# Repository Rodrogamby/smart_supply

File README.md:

# Dashboard

Dashboard for the project, built with HTML, CSS, JavaScript, Vite, and MQTT.js

The current prototype displays real sensor readings from an ESP32-S3 in the Channel 1 area

## Requirements

- Install [Node.js](https://nodejs.org/) with npm 
- An internet connection to reach the MQTT broker already running on Azure
- An ESP32 publishing measurements to see live readings

## Install and run

Open a terminal in the GUI folder containing `package.json`.

```sh
npm install
npm run dev
```

`npm install` installs the project's dependencies, including Vite and MQTT.js, and creates `node_modules`. 

Open the local URL printed by Vite. Keep the terminal running while using the dashboard. Press **Ctrl+C** to stop it; use `npm run dev` to start it again.

## Connect to MQTT

Enter these values in the dashboard and click **Connect**:

| Setting | Value |
| --- | --- |
| WebSocket URL | `wss://retotest.mexicocentral.cloudapp.azure.com:8084/mqtt` |
| Current test username | `reto` |
| Current test password | `reto` |
| Topic used by the JavaScript | `test2` |

These are temporary lol

The ESP32 sends MQTT over TLS on port **8883**. The browser uses MQTT over secure WebSockets on port **8084** to connect to the same broker.

## Measurement format

The ESP32 publishes JSON messages like this on `test2`:

```json
{
  "device": "device",
  "sensor": "sensor",
  "sample": 1,
  "adc_raw": 25798
}
```

## Project files

| File | Purpose |
| --- | --- |
| `index.html` | Dashboard structure |
| `src/style.css` | Styling and responsive layout |
| `src/main.js` | MQTT connection, message validation, and display updates |
| `package.json` | Dependencies and npm commands |
| `package-lock.json` | Locked dependency versions |

# Access the Virtual Machine

Use Tec Visitantes Network

```cmd
ssh -i "path of the  smart_supply\VM\vm1_key.pem file" azureuser@158.23.60.51
```

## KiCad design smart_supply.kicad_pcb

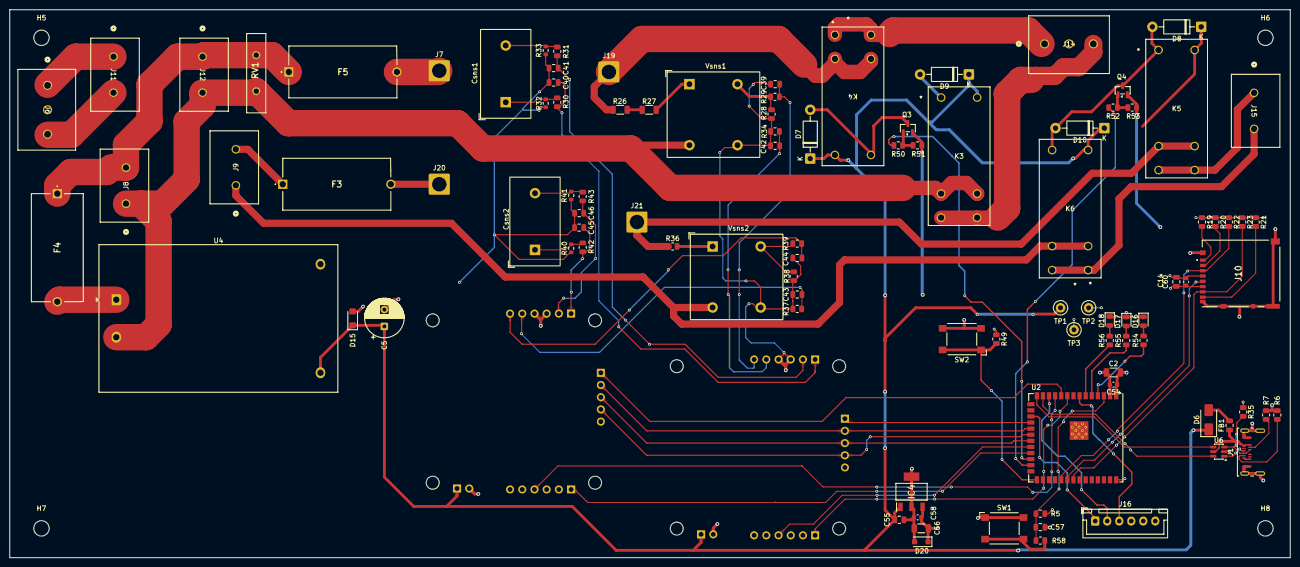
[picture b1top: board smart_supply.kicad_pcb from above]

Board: 4 copper layers, 266.5 x 114.0 mm, 106 parts (0 on the bottom side), 76 nets.

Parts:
C2: 22u; C_1206_3216Metric
C5: 220u; CP_Radial_D8.0mm_P3.50mm
C14: 10u; C_0805_2012Metric
C39, C40, C41, C42, C43, C44, C45, C46: 33n; C_0805_2012Metric
C54, C58, C60: 100n; C_0603_1608Metric
C55: 4.7u; C_0805_2012Metric
C56: 10u; C_1206_3216Metric
C57: 1uF; C_0805_2012Metric
Csns1, Csns2: ZMCT103C; Transformer_Zeming_ZMCT103C
D6: SS34; D_SMA
D7, D8, D9, D10: 1N4007; D_DO-41_SOD81_P10.16mm_Horizontal
D15: SMF5V0A; D_SMF
D16, D17, D18: LED; LED_0805_2012Metric
D20: SMF3.3; D_SOD-123F
F3, F4, F5: Fuse; fuse holder
FB1: FerriteBead; C_0805_2012Metric
H5, H6, H7, H8: MountingHole; MountingHole_3.2mm_M3
IC4: MIC39100-3.3WS; SOT230P700X180-4N
J1: USB_C_Receptacle_USB2.0_16P; USB_C_Receptacle_Amphenol_124019772112A
J6, J14: 1730405; CONN_1730405_PXC
J7, J19, J20, J21: Conn_01x01; SolderWire-2.5sqmm_1x01_D2.4mm_OD4.4mm
J8, J9, J11, J12, J15: 1717020; CONN_1717020_PXC
J10: DM3AT-SF-PEJM5; DM3ATSFPEJM5
J16: Conn_01x06_Pin; JST_XH_B6B-XH-A_1x06_P2.50mm_Vertical
J17, J18: Conn_01x19_Pin; breakoutHOLES
K3, K4, K5, K6: G2R-1A-E DC5; RELAY_G2R-1A-E AC12_OMR
Q3, Q4: AO3400A; SOT-23
R5, R19, R20, R21, R22, R23, R49: 10k; R_0805_2012Metric
R6, R7: 5.1k; R_0805_2012Metric
R26, R27: 47k; R_1206_3216Metric
R28, R38, R50, R52: 100; R_0805_2012Metric
R29, R30, R31, R34, R37, R39, R42, R43: 1k; R_0805_2012Metric
R32, R33: 10; R_0603_1608Metric
R35: 1.5k; R_0805_2012Metric
R36: 20k; R_0805_2012Metric
R40, R41: 33; R_0603_1608Metric
R51, R53: 100k; R_0805_2012Metric
R54, R55, R56, R58: 470; R_0805_2012Metric
RV1: MOV-14D241K; MOV14D241K
SW1, SW2: SW_Push; SW_SPST_Omron_B3FS-100xP
TP1, TP2, TP3: TestPoint; TestPoint_Loop_D2.50mm_Drill1.0mm
U2: ESP32-S3-WROOM-1U
U4: HLK-10M05; Converter_ACDC_Hi-Link_HLK-10Mxx
U6: USBLC6-2SC6; SOT-23-6
Vsns1, Vsns2: ZMPT101K; Transformer_Zeming_ZMPT101K

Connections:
+3.3V: C2.1, C14.1, C54.1, C56.1, C58.2, C60.2, D20.1 (A1), IC4.3 (OUT), J10.4 (VDD), R5.2, R19.1, R20.1, R21.1, R22.1, R23.1, R35.1, R49.1, TP2.1 (1_1), U2.2 (3V3)
+5V: C5.1, C55.1, D6.1 (K), D7.1 (K), D8.1 (K), D9.1 (K), D10.1 (K), D15.1 (A1), IC4.1 (IN), J17.19, J18.19, K3.8, K4.8, K5.8, K6.8, TP1.1 (1_1), U4.4 (+Vout)
/MCU/BOOT: R49.2, SW2.1, U2.27 (IO0)
/MCU/CLK_SD: J10.5 (CLK), U2.32 (IO39)
/MCU/CMD: J10.3 (CMD), R22.2, U2.31 (IO38)
/MCU/D0_SD: J10.7 (DAT0), R23.2, U2.33 (IO40)
/MCU/DAT1: J10.8 (DAT1), R21.2
/MCU/DAT2: J10.1 (DAT2), R19.2
/MCU/DAT3: J10.2 (CD/DAT3), R20.2
/MCU/EN: C57.2, R5.1, R58.2, U2.3 (EN)
/MCU/FUSEL: F4.2, U4.1 (AC/L)
/MCU/LEDF: R55.1, U2.5 (IO5)
/MCU/LEDSD: R56.1, U2.6 (IO6)
/MCU/LEDW: R54.1, U2.4 (IO4)
/MCU/USB_D+: U2.14 (USB_D+), U6.4 (I/O2)
/MCU/USB_D-: U2.13 (USB_D-), U6.6 (I/O1)
/MCU/VBUS: FB1.1, J1.A4 (VBUS), J1.A9 (VBUS), J1.B4 (VBUS), J1.B9 (VBUS), U6.5 (VBUS)
/POWER LINES/CH1_L_OUT: J14.1, K4.4, K4.5
/POWER LINES/CH1_N_OUT: J14.3, K3.4, K3.5
/POWER LINES/CH2_L: J21.1 (Pin_1_1), K5.3, K5.6, R36.1
/POWER LINES/CH2_L_OUT: J15.1, K5.4, K5.5
/POWER LINES/CH2_N: J9.1, K6.3, K6.6, Vsns2.2
/POWER LINES/CH2_N_OUT: J15.2, K6.4, K6.5
/POWER LINES/CT1_1: F5.2, J7.1 (Pin_1_1)
/POWER LINES/CT1_2: F3.2, J20.1 (Pin_1_1)
/POWER LINES/L: J6.1, J11.1
/POWER LINES/N: J6.3, J11.2
/POWER LINES/csns1P1: Csns1.1, R30.2, R32.1
/POWER LINES/csns1P2: Csns1.2, R31.2, R33.2
/POWER LINES/csns2P1: Csns2.1, R40.1, R42.2
/POWER LINES/csns2P2: Csns2.2, R41.2, R43.2
ACDCsupply: F4.1, F5.1, J8.2, J12.1, RV1.2
CH1_L: J19.1 (Pin_1_1), K4.3, K4.6, R26.1
CH1_N: J8.1, J12.2, K3.3, K3.6, RV1.1, U4.2 (AC/N), Vsns1.2
CS1: J17.7, U2.18 (IO10)
CS2: J18.7, U2.10 (IO17)
GND: C2.2, C5.2, C14.2, C39.2, C40.2, C41.2, C42.2, C43.2, C44.2, C45.2, C46.2, C54.2, C55.2, C56.2, C57.1, C58.1, C60.1, D15.2 (A2), D16.1 (K), D17.1 (K), D18.1 (K), D20.2 (A2), IC4.2 (GND_1), IC4.4 (GND_2), J1.A1 (GND), J1.A12 (GND), J1.B1 (GND), J1.B12 (GND), J1.SH (SHIELD), J10.6 (VSS), J10.MP1, J10.MP2, J10.MP3, J10.MP4, J10.MP5, J10.MP6, J16.6, J17.3, J17.4, J17.18, J18.3, J18.4, J18.18, Q3.2 (S), Q4.2 (S), R6.2, R7.2, R28.1, R32.2, R33.1, R34.2, R37.2, R38.2, R40.2, R41.1, R51.2, R53.2, SW1.1, SW2.2, TP3.1 (1_1), U2.1 (GND), U2.40 (GND), U2.41 (GND), U4.3 (-Vout), U6.2 (GND), Vsns1.3, Vsns2.3
IAN1: C41.1, J17.2, R31.1
IAN2: C46.1, J18.2, R43.1
IAP1: C40.1, J17.1, R30.1
IAP2: C45.1, J18.1, R42.1
IRQ1: J17.15, U2.22 (IO14)
IRQ2: J18.15, U2.11 (IO18)
LED1: J16.3, U2.7 (IO7)
LED2: J16.2, U2.12 (IO8)
LED3: J16.1, U2.17 (IO9)
MISO: J17.9, J18.9, U2.21 (IO13)
MOSI: J17.8, J18.8, U2.19 (IO11)
unnamed: D6.2 (A), FB1.2
unnamed: D7.2 (A), D9.2 (A), K3.1, K4.1, Q3.3 (D)
unnamed: D8.2 (A), D10.2 (A), K5.1, K6.1, Q4.3 (D)
unnamed: D16.2 (A), R54.2
unnamed: D17.2 (A), R55.2
unnamed: D18.2 (A), R56.2
unnamed: F3.1, J9.2
unnamed: J1.A5 (CC1), R6.1
unnamed: J1.B5 (CC2), R7.1
unnamed: J1.A6 (D+), J1.B6 (D+), R35.2, U6.3 (I/O2)
unnamed: J1.A7 (D-), J1.B7 (D-), U6.1 (I/O1)
unnamed: Q3.1 (G), R50.1, R51.1
unnamed: Q4.1 (G), R52.1, R53.1
unnamed: R26.2, R27.1
unnamed: R27.2, Vsns1.1
unnamed: R28.2, R29.2, Vsns1.4
unnamed: R36.2, Vsns2.1
unnamed: R38.1, R39.1, Vsns2.4
unnamed: R58.1, SW1.2
RLY_CH1: R50.2, U2.24 (IO47)
RLY_CH2: R52.2, U2.25 (IO48)
SCLK: J17.10, J18.10, U2.20 (IO12)
VN1: C42.1, J17.5, R34.1
VN2: C43.1, J18.5, R37.1
VP1: C39.1, J17.6, R29.1
VP2: C44.1, J18.6, R39.2
ZX1: J17.12, U2.9 (IO16)
ZX2: J18.12, U2.23 (IO21)

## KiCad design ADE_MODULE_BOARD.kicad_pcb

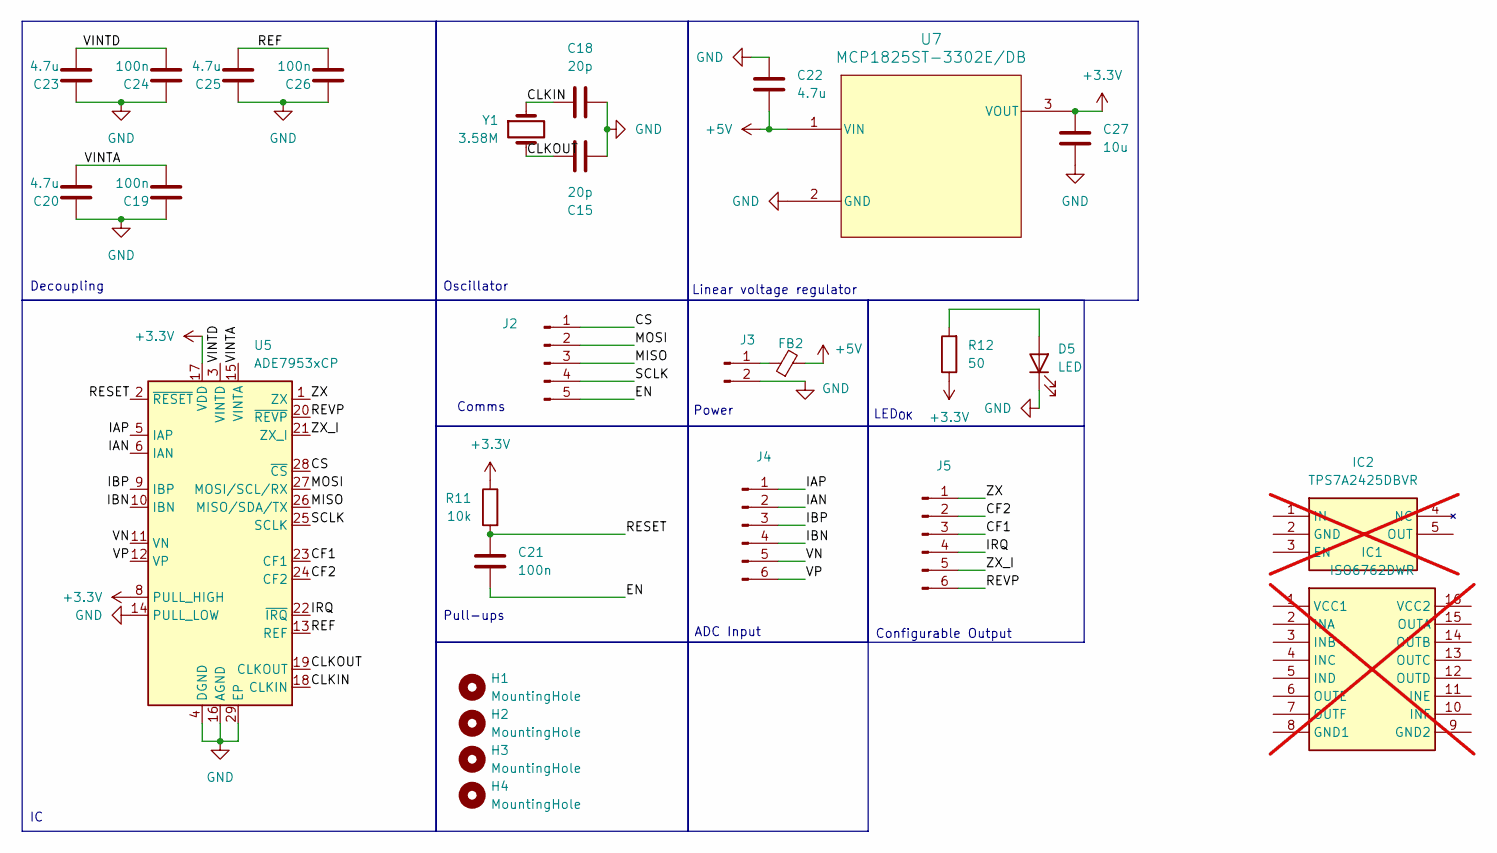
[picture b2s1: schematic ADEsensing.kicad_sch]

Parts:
C15, C18: 20p; C_0603_1608Metric; MPN C165732
C19, C21, C24, C26: 100n; C_0603_1608Metric; MPN C1590
C20, C22, C23, C25: 4.7u; C_0805_2012Metric; MPN C1779
C27: 10u; C_0805_2012Metric; MPN C15850
D5: LED; LED_0805_2012Metric; MPN C2986046
FB2: FerriteBead_Small; L_0805_2012Metric; MPN C1015
H1, H2, H3, H4: MountingHole; MountingHole_2.7mm_M2.5
IC1: ISO6762DWR; SOIC127P1030X265-16N; Mouser Part Number 595-ISO6762DWR; not fitted
IC2: TPS7A2425DBVR; SOT95P280X145-5N; Mouser Part Number 595-TPS7A2425DBVR; not fitted
J2: Conn_01x05_Pin; PinHeader_1x05_P2.54mm_Vertical
J3: Conn_01x02_Pin; PinHeader_1x02_P2.54mm_Vertical
J4, J5: Conn_01x06_Pin; PinHeader_1x06_P2.54mm_Vertical
R11: 10k; R_0805_2012Metric; MPN C17414
R12: 50; R_0805_2012Metric; MPN C55205334
U5: ADE7953xCP; LFCSP-28-1EP_5x5mm_P0.5mm_EP3.14x3.14mm_ThermalVias; MPN C515890
U7: MCP1825ST-3302E/DB; SOT-223-3_TabPin2; MPN C145411
Y1: 3.58M; Crystal_SMD_HC49-SD; MPN C22464956

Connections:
+3.3V: C27.1, R11.1, R12.1, U5.7 (PULL_HIGH), U5.8 (PULL_HIGH), U5.17 (VDD), U7.3 (VOUT)
+5V: C22.2, FB2.2, U7.1 (VIN)
/ADE Module/CF1: J5.3, U5.23 (CF1)
/ADE Module/CF2: J5.2, U5.24 (CF2)
/ADE Module/CLKIN: C18.1, U5.18 (CLKIN), Y1.1
/ADE Module/CLKOUT: C15.2, U5.19 (CLKOUT), Y1.2
/ADE Module/CS: J2.1, U5.28 (~CS)
/ADE Module/EN: C21.2, J2.5
/ADE Module/IAN: J4.2, U5.6 (IAN)
/ADE Module/IAP: J4.1, U5.5 (IAP)
/ADE Module/IBN: J4.4, U5.10 (IBN)
/ADE Module/IBP: J4.3, U5.9 (IBP)
/ADE Module/IRQ: J5.4, U5.22 (~IRQ)
/ADE Module/MISO: J2.3, U5.26 (MISO/SDA/TX)
/ADE Module/MOSI: J2.2, U5.27 (MOSI/SCL/RX)
/ADE Module/REF: C25.2, C26.2, U5.13 (REF)
/ADE Module/RESET: C21.1, R11.2, U5.2 (~RESET)
/ADE Module/REVP: J5.6, U5.20 (~REVP)
/ADE Module/SCLK: J2.4, U5.25 (SCLK)
/ADE Module/VINTA: C19.2, C20.2, U5.15 (VINTA)
/ADE Module/VINTD: C23.2, C24.2, U5.3 (VINTD)
/ADE Module/VN: J4.5, U5.11 (VN)
/ADE Module/VP: J4.6, U5.12 (VP)
/ADE Module/ZX: J5.1, U5.1 (ZX)
/ADE Module/ZX_I: J5.5, U5.21 (ZX_I)
GND: C15.1, C18.2, C19.1, C20.1, C22.1, C23.1, C24.1, C25.1, C26.1, C27.2, D5.1 (K), J3.2, U5.4 (DGND), U5.14 (PULL_LOW), U5.16 (AGND), U5.29 (EP), U7.2 (GND)
unnamed: D5.2 (A), R12.2
unnamed: FB2.1, J3.1

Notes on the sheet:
Configurable Output
Oscillator
Power
Comms
Linear voltage regulator
Pull-ups
LED_{OK}
ADC Input
Decoupling

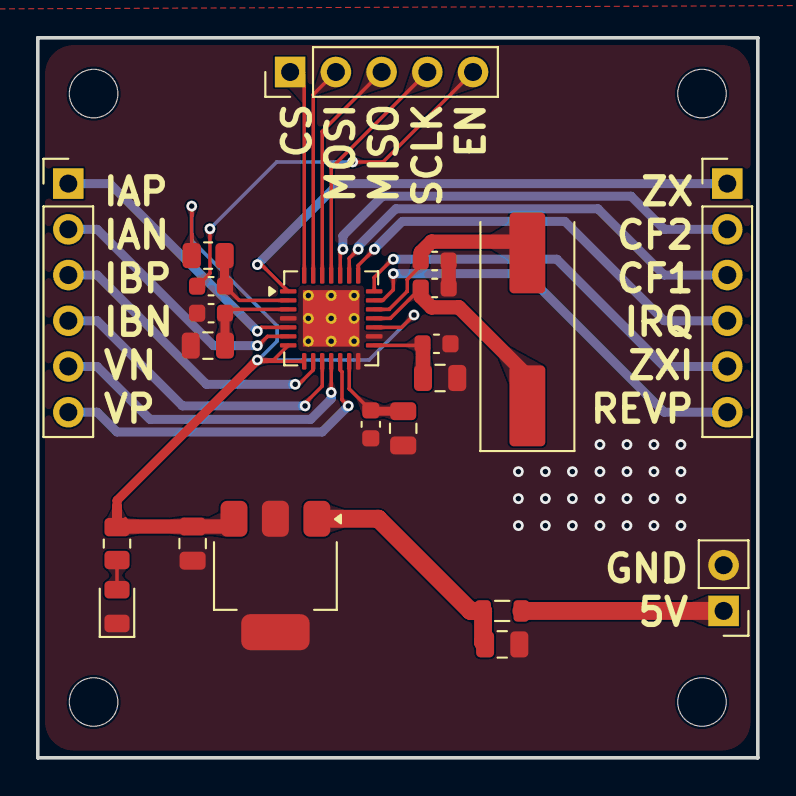
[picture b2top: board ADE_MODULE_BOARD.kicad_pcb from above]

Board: 2 copper layers, 40.0 x 40.0 mm, 26 parts (0 on the bottom side), 28 nets.
